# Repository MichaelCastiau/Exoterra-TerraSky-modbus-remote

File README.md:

# Exoterra Terrasky IR modbus enabled remote

These are the hardware schematics for a STM32 powered 38kHz IR remote that can 'learn' and then send out specfic signals for day, night and twilight lighting effects for the Exo Terrasky light. It makes use of the NEC protocol to learn and send commands.

The purpose is to automate an ExoTerra Terrasky using IR, since the default remote control doesn't have any timers.

RS-485 Modbus RTU can be used to send commands to change the lights, using a Modbus enabled PLC.

**The schematics are drawn using KiCad**

The firmware repository can be found [here](https://github.com/MichaelCastiau/Exoterra-Terrasky-modbus-remote-firmware/).

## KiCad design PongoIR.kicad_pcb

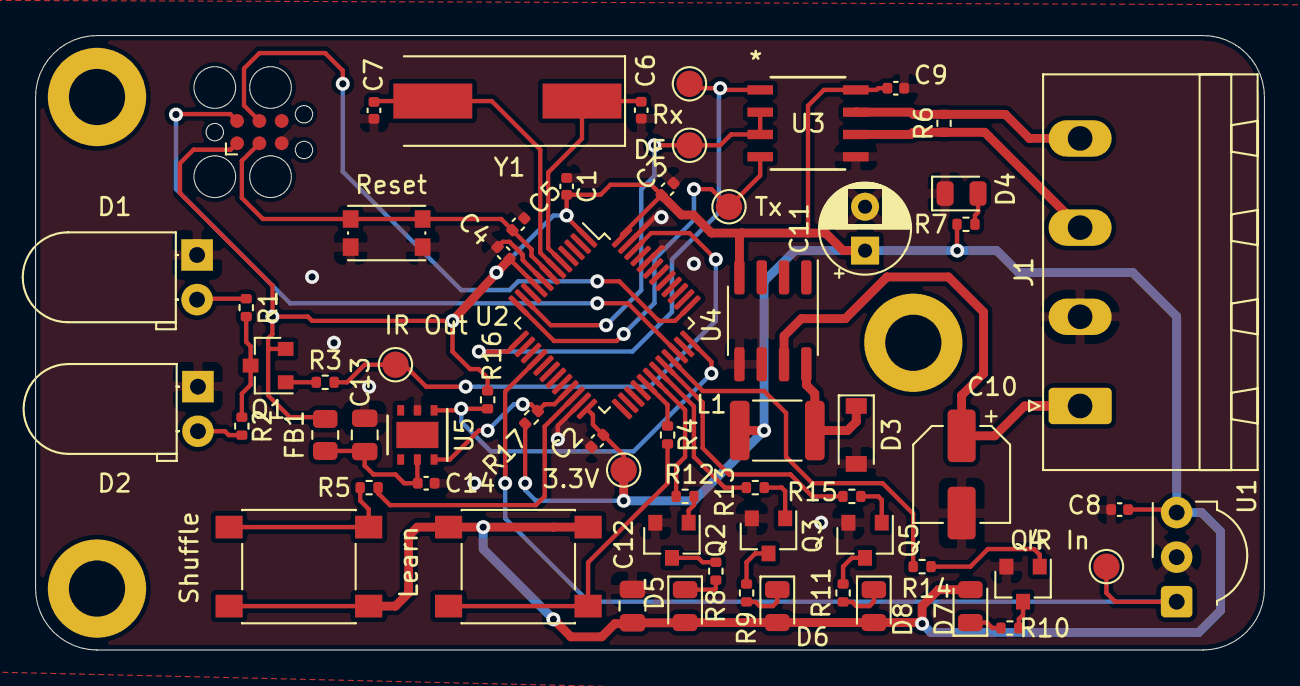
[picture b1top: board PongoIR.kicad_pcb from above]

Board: 2 copper layers, 70.0 x 35.0 mm, 66 parts (0 on the bottom side), 44 nets.

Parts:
C1, C2, C3, C4, C5, C8, C9, C14: 0.1uF; C_0402_1005Metric
C6, C7: 15pF; C_0402_1005Metric
C10: 68uF; CP_Elec_5x5.4
C11: 120uF; CP_Radial_D5.0mm_P2.50mm
C12, C13: 22uF; C_0805_2012Metric
D1, D2: LED; LED_D5.0mm_Horizontal_O1.27mm_Z3.0mm_IRGrey
D3: 1N5817; D_SOD-123
D4: Power On (Green); LED_0805_2012Metric
D5: Learn (Orange); LED_0805_2012Metric
D6: Day (yellow); LED_0805_2012Metric
D7: Night (yellow); LED_0805_2012Metric
D8: Twilight (yellow); LED_0805_2012Metric
FB1: Ferrite_Bead; R_0805_2012Metric
H1, H2, H3: MountingHole; MountingHole_3.2mm_M3_DIN965_Pad
J1: Conn_01x04; PhoenixContact_MSTBA_2,5_4-G-5,08_1x04_P5.08mm_Horizontal
J2: Conn_01x06; Tag-Connect_TC2030-IDC-FP_2x03_P1.27mm_Vertical
L1: 100uH; L_1812_4532Metric
Q1: BC807; SOT-23
Q2, Q3, Q4, Q5: 2N7002; SOT-23
R1, R2: 86R; R_0402_1005Metric
R3, R16, R17: 5k6; R_0402_1005Metric
R4, R5: 10k; R_0402_1005Metric
R6: 120; R_0402_1005Metric
R7, R8, R9, R10, R11: 60R; R_0402_1005Metric
R12, R13, R14, R15: 1M; R_0402_1005Metric
SW1: Reset; SW_Push_1P1T_NO_CK_KMR2
SW2: Learn; SW_Push_1P1T_NO_6x6mm_H9.5mm
SW3: Shuffle; SW_Push_1P1T_NO_6x6mm_H9.5mm
TP1: IR In; TestPoint_Pad_D1.5mm
TP2: IR Out; TestPoint_Pad_D1.5mm
TP3: DE; TestPoint_Pad_D1.5mm
TP4: Tx; TestPoint_Pad_D1.5mm
TP5: Rx; TestPoint_Pad_D1.5mm
TP6: 3.3V; TestPoint_Pad_D1.5mm
U1: TSOP348xx; Vishay_MOLD-3Pin
U2: STM32F030C6Tx; LQFP-48_7x7mm_P0.5mm
U3: MAX14776EASA+; MAX14776E
U4: LM2594HVM-3.3; SOIC-8_3.9x4.9mm_P1.27mm
U5: HDC1080; Texas_PWSON-N6
Y1: 16MHz; Crystal_SMD_HC49-SD

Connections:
+3V3: C1.2, C2.2, C3.2, C4.2, C8.1, C9.2, C11.1, C12.1, D5.2, D6.2, D7.2, D8.2, FB1.1, J2.1, L1.2, Q1.2, R7.1, R16.1, R17.1, SW2.1, SW3.1, TP6.1, U1.3, U2.1, U2.9, U2.24, U2.48, U3.8, U4.4
+24V: C10.1, J1.1, U4.7
/I2C_SCL: R17.2, U2.21, U5.6
/I2C_SDA: R16.2, U2.36, U5.1
/IR_OUT: R3.1, TP2.1, U2.46
/NRST: C5.1, J2.3, SW1.2, U2.7
/SWD_CLK: J2.4, U2.37
/SWD_IO: J2.2, U2.34
/SW_LEARN: R4.1, U2.29
/SW_SHUFFLE: R5.1, U2.22
/USART_DE: TP3.1, U2.11, U3.2, U3.3
/USART_RX: TP5.1, U2.13, U3.1
/USART_TX: TP4.1, U2.12, U3.4
/leds/LED_DAY: R13.2, U2.31
/leds/LED_LEARN: R12.2, U2.30
/leds/LED_NIGHT: R15.2, U2.32
/leds/LED_TWILIGHT: R14.2, U2.33
GND: C1.1, C2.1, C3.1, C4.1, C5.2, C6.2, C7.2, C8.2, C9.1, C10.2, C11.2, C12.2, C13.1, C14.1, D1.1, D2.1, D3.2, D4.1, J1.2, J2.5, Q2.2, Q3.2, Q4.2, Q5.2, SW1.1, U1.2, U2.8, U2.23, U2.44, U2.47, U3.5, U4.5, U4.6, U5.2
unnamed: C6.1, U2.5, Y1.1
unnamed: C7.1, U2.6, Y1.2
unnamed: C13.2, C14.2, FB1.2, U5.5
unnamed: D1.2, R1.2
unnamed: D2.2, R2.2
unnamed: D3.1, L1.1, U4.8
unnamed: D4.2, R7.2
unnamed: D5.1, R8.1
unnamed: D6.1, R9.1
unnamed: D7.1, R10.1
unnamed: D8.1, R11.1
unnamed: Q1.1, R3.2
unnamed: Q1.3, R1.1, R2.1
unnamed: Q2.1, R12.1
unnamed: Q2.3, R8.2
unnamed: Q3.1, R13.1
unnamed: Q3.3, R9.2
unnamed: Q4.1, R14.1
unnamed: Q4.3, R10.2
unnamed: Q5.1, R15.1
unnamed: Q5.3, R11.2
unnamed: R4.2, SW2.2
unnamed: R5.2, SW3.2
unnamed: TP1.1, U1.1, U2.16
RS485_A: J1.3, R6.1, U3.6
RS485_B: J1.4, R6.2, U3.7

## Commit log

2022-05-02 change IR leds to NPN transistor

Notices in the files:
parts and their libraries:
Copyright 2016 Accelerated Designs. All rights reserved.
